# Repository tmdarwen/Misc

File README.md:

Miscellaneous Repo
==================

This is a repo for my smaller projects that don't really belong in any of my other repos.

**Index**
-   [**CS4334BreakoutBoard**](CS4334BreakoutBoard/README.md): A Cirrus Logic [CS4334](https://www.cirrus.com/products/cs4334-35-38-39/) audio DAC breakout circuit board I created using KiCad.
-   [**TivaMAX5136**](TivaMAX5136/README.md): Shows how to use [SPI](https://en.wikipedia.org/wiki/Serial_Peripheral_Interface) communication on the [Texas Instruments "Tiva" EK-TM4C1294XL evaluation board](https://www.ti.com/tool/EK-TM4C1294XL) with a 16 bit *stereo* audio [DAC](https://en.wikipedia.org/wiki/Digital-to-analog_converter).
-   [**TivaMAX541**](TivaMAX541/README.md): Shows how to use [SPI](https://en.wikipedia.org/wiki/Serial_Peripheral_Interface) communication on the [Texas Instruments "Tiva" EK-TM4C1294XL evaluation board](https://www.ti.com/tool/EK-TM4C1294XL) with a 16 bit audio [DAC](https://en.wikipedia.org/wiki/Digital-to-analog_converter).
-   [**TivaSPI**](TivaSPI/README.md): Shows how to use [SPI](https://en.wikipedia.org/wiki/Serial_Peripheral_Interface) communication on the [Texas Instruments "Tiva" EK-TM4C1294XL evaluation board](https://www.ti.com/tool/EK-TM4C1294XL) with an IO Expander.

**Licensing**

The MIT License applies to this software and its supporting documentation:

*Copyright (c) 2020-2021 - Terence M. Darwen - tmdarwen.com*

*Permission is hereby granted, free of charge, to any person obtaining a copy of
this software and associated documentation files (the "Software"), to deal in
the Software without restriction, including without limitation the rights to
use, copy, modify, merge, publish, distribute, sublicense, and/or sell copies of
the Software, and to permit persons to whom the Software is furnished to do so,
subject to the following conditions:*

*The above copyright notice and this permission notice shall be included in all
copies or substantial portions of the Software.*

*THE SOFTWARE IS PROVIDED "AS IS", WITHOUT WARRANTY OF ANY KIND, EXPRESS OR
IMPLIED, INCLUDING BUT NOT LIMITED TO THE WARRANTIES OF MERCHANTABILITY, FITNESS
FOR A PARTICULAR PURPOSE AND NONINFRINGEMENT. IN NO EVENT SHALL THE AUTHORS OR
COPYRIGHT HOLDERS BE LIABLE FOR ANY CLAIM, DAMAGES OR OTHER LIABILITY, WHETHER
IN AN ACTION OF CONTRACT, TORT OR OTHERWISE, ARISING FROM, OUT OF OR IN
CONNECTION WITH THE SOFTWARE OR THE USE OR OTHER DEALINGS IN THE SOFTWARE.*

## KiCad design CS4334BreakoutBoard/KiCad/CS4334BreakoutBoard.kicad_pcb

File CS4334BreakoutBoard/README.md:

CS4334 Audio DAC Breakout Board
===============================

A repo for the KiCad files for my [CS4334](https://www.cirrus.com/products/cs4334-35-38-39/) Audio DAC breakout board.  More info about this project can be found on my website [here](https://tmdarwen.com/creating-a-circuit-board-from-scratch.html).  After manufacturing and assembling this breakout board I was able to send it audio (I2S) using an STM32F411 development board running software I wrote that can be found [here](https://github.com/tmdarwen/STM32/tree/master/STM32F411/OnboardAudioOutput).

**Schematic**

**Bill of Materials**

| Schematic Part | Manufacturer    | Part              | Description                              | 
| ---------------| --------------- |-------------------|------------------------------------------|
| C1             | AVX Corporation | 08055C104K4T4A    | 1uF X7R Surface Mount Capacitor          |
| C2,C3          | Panasonic       | EEE-HA1H3R3R      | 3.3uF Surface Mount Capacitor            |
| C4             | Panasonic       | EEE-HD1C100AR     | 10uF Surface Mount Capacitor             |
| C5,C6,C7,C8    | Panasonic       | CC0805KRX7R0BB152 | 1500pF Surface Mount Capacitor           |
| D1             | Yageo           | LG R971-KN-1      | Surface Mount Green LED                  |
| J1             | N/A             | N/A               | 6 Male Header Pins                       |
| J2             | CUI Devices     | CP-3523SJCT-ND    | 3.5mm Stereo Audio Jack                  |
| L1             | Taiyo Yudens    | FBMH2012HM121-T   | 120 Ohms @ 100 MHz Ferrite Bead Inductor |
| R1             | Yageo           | YAG2328CT-NDD     | 1K Surface Mount Resistor                |
| R2,R3          | Yageo           | RT0805DRE07267KL  | 267K Surface Mount Resistor              |
| R4,R5          | Yageo           | AC0805FR-0710KL   | 10K Surface Mount Resistor               |
| R6,R7          | Yageo           | AC0805JR-07560RL  | 560 Surface Mount Resistor               |
| U1             | Cirrus Logic    | CS4334-DSZ        | 16 Bit Stereo Audio DAC                  |

**Additional Pics**

The manufactured board unassembled:

The PCB layout I made in KiCad without the front copper:

The PCB layout with the front copper:

**Licensing**

The MIT License applies to this software and its supporting documentation:

*Copyright (c) 2021 Terence M. Darwen - tmdarwen.com*

*Permission is hereby granted, free of charge, to any person obtaining a copy of
this software and associated documentation files (the "Software"), to deal in
the Software without restriction, including without limitation the rights to
use, copy, modify, merge, publish, distribute, sublicense, and/or sell copies of
the Software, and to permit persons to whom the Software is furnished to do so,
subject to the following conditions:*

*The above copyright notice and this permission notice shall be included in all
copies or substantial portions of the Software.*

*THE SOFTWARE IS PROVIDED "AS IS", WITHOUT WARRANTY OF ANY KIND, EXPRESS OR
IMPLIED, INCLUDING BUT NOT LIMITED TO THE WARRANTIES OF MERCHANTABILITY, FITNESS
FOR A PARTICULAR PURPOSE AND NONINFRINGEMENT. IN NO EVENT SHALL THE AUTHORS OR
COPYRIGHT HOLDERS BE LIABLE FOR ANY CLAIM, DAMAGES OR OTHER LIABILITY, WHETHER
IN AN ACTION OF CONTRACT, TORT OR OTHERWISE, ARISING FROM, OUT OF OR IN
CONNECTION WITH THE SOFTWARE OR THE USE OR OTHER DEALINGS IN THE SOFTWARE.*

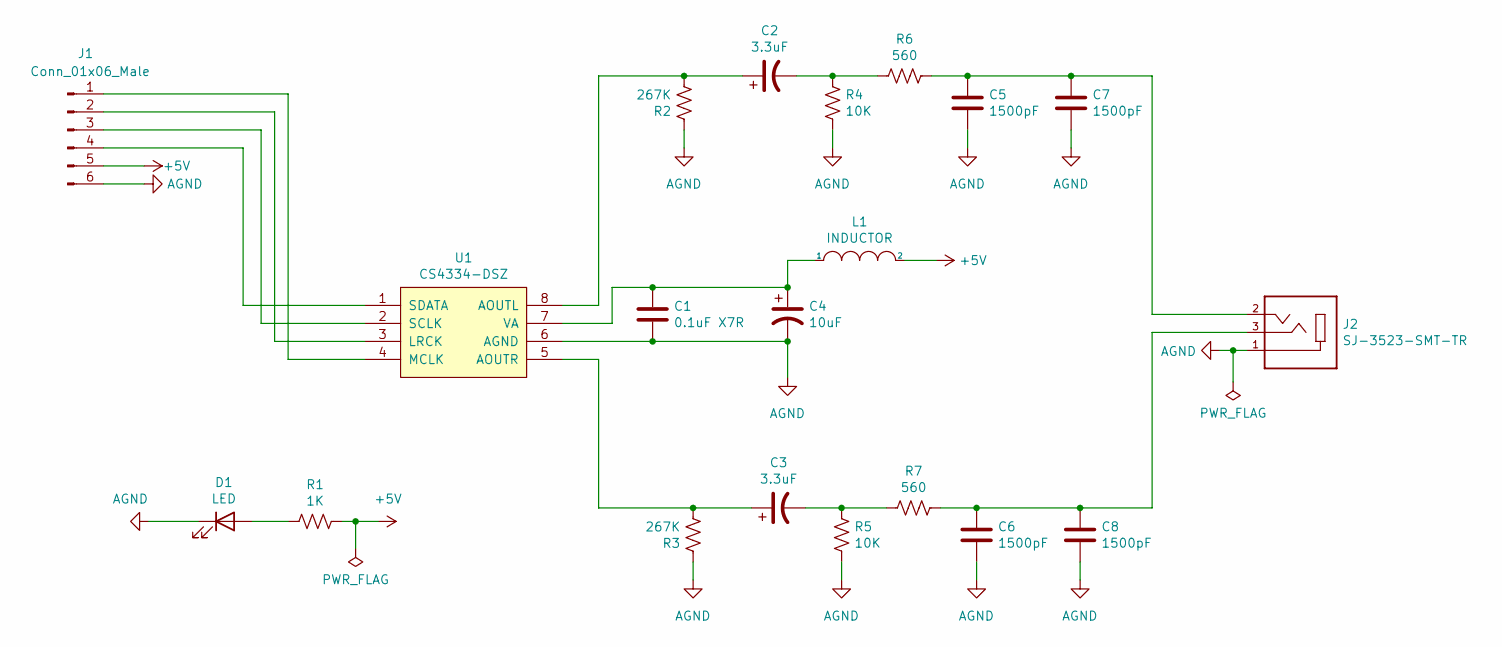
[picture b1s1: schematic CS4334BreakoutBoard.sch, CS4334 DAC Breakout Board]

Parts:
C1: 0.1uF X7R; C_0805_2012Metric_Pad1.18x1.45mm_HandSolder; MFG# 08055C104K4T4A; Digikey 478-10546-1-ND
C2, C3: 3.3uF; TMD_CP_Elec_4x5.4; MFG# EEE-HA1H3R3R; Digikey PCE4219CT-ND
C4: 10uF; TMD_CP_Elec_4x5.8; mfg# EEE-HD1C100AR; digikey PCE4949CT-ND
C5, C6, C7, C8: 1500pF; C_0805_2012Metric_Pad1.18x1.45mm_HandSolder; MFG# CC0805KRX7R0BB152; Digikey 311-4302-1-ND
D1: LED; LED_0805_2012Metric_Pad1.15x1.40mm_HandSolder; MFG# LG R971-KN-1; Digikey 475-1410-1-ND
J1: Conn_01x06_Male; TMD_PinHeader_1x06_P2.54mm_Vertical
J2: SJ-3523-SMT-TR; TMD_Switch_Slide_11.6x4mm_SJ-3523-SMT; MFG# CP-3523SJCT-ND; Digikey SJ-3523-SMT-TR
L1: INDUCTOR; L_0805_2012Metric_Pad1.15x1.40mm_HandSolder; MFG# FBMH2012HM121-T; Digikey 587-1747-1-ND
R1: 1K; R_0805_2012Metric_Pad1.20x1.40mm_HandSolder; MFG# RT0805BRE071KL; Digikey YAG2328CT-ND
R2, R3: 267K; R_0805_2012Metric_Pad1.20x1.40mm_HandSolder; MFG# RT0805DRE07267KL; Digikey 311-2834-1-ND
R4, R5: 10K; R_0805_2012Metric_Pad1.20x1.40mm_HandSolder; MFG# AC0805FR-0710KL; Digikey 311-10KLGCT-ND
R6, R7: 560; R_0805_2012Metric_Pad1.20x1.40mm_HandSolder; MFG# AC0805JR-07560RL; Digikey YAG3799CT-ND
U1: CS4334-DSZ; SO-8_3.9x4.9mm_P1.27mm_TMD; MFG# CS4334-DSZ; Digikey 598-1631-ND

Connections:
+5V: J1.5, L1.2, R1.1
GNDA: C1.2, C4.2, C5.2, C6.2, C7.2, C8.2, D1.1 (K), J1.6, J2.1, R2.1, R3.1, R4.2, R5.2, U1.6 (AGND)
unnamed: C1.1, C4.1, L1.1, U1.7 (VA)
unnamed: C2.1, R2.2, U1.8 (AOUTL)
unnamed: C2.2, R4.1, R6.2
unnamed: C3.1, R3.2, U1.5 (AOUTR)
unnamed: C3.2, R5.1, R7.2
unnamed: C5.1, C7.1, J2.2, R6.1
unnamed: C6.1, C8.1, J2.3, R7.1
unnamed: D1.2 (A), R1.2
unnamed: J1.1, U1.4 (MCLK)
unnamed: J1.2, U1.3 (LRCK)
unnamed: J1.3, U1.2 (SCLK)
unnamed: J1.4, U1.1 (SDATA)

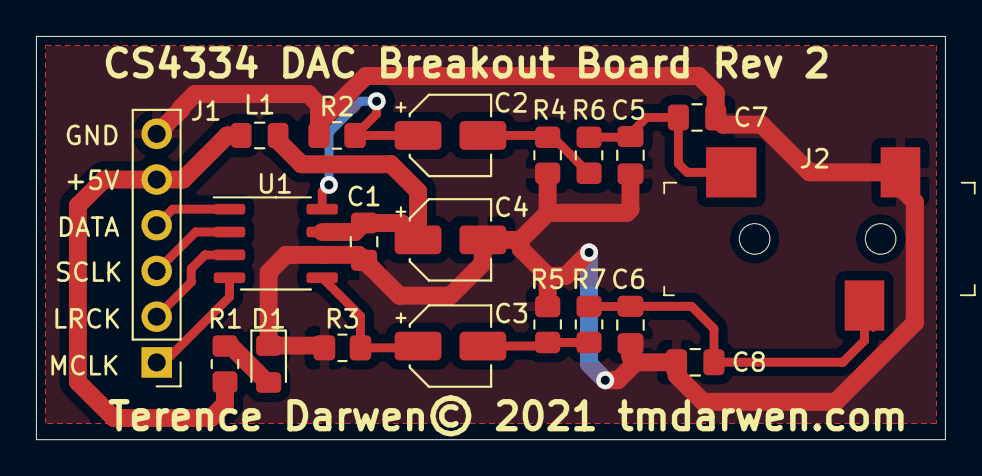
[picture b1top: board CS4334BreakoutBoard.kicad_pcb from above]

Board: 2 copper layers, 50.5 x 22.4 mm, 20 parts (0 on the bottom side), 14 nets.

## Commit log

2020-12-07 Adding TivaSPI project
2020-12-07 Minor typo and formatting updates
2020-12-25 Adding example of TI Tiva TM4C1294 dev board sending digital audio to a 16 bit DAC (MAX541).
2020-12-25 Fixed some typos in the readme.
2020-12-25 Adding general readme for this repo.
2020-12-29 A bit of amplification on the audio signal and some minor tweaks to the project files.
2020-12-29 Adding a very small wave file as an easy-to-listen-to sample of the audio being send from the Tiva to the DAC.
2020-12-29 Fix to typo in readme.
2021-01-10 Updated the schematic to include op amp and voltage divider.
2021-01-10 Minor wording and format changes to the readme.
2021-03-07 Adding Tiva MAX5136 project
2021-03-07 Updating README with new project.
2021-03-07 Fixed incorrect DAC chip name.
2021-03-07 Fix to the TivaMAX5136 schematic.
2021-07-11 Adding CS4334 Breakout Board project.
2021-07-11 Modifications to table formatting.
2021-07-11 Readme formatting.
2021-07-11 Update README.md
    Fixed typo.
2024-06-22 Update README.md fi
2024-06-22 Update README.md fixing broken link.

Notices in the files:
CS4334BreakoutBoard/KiCad/CS4334BreakoutBoard.kicad_pcb:
Terence Darwen© 2021 tmdarwen.com
